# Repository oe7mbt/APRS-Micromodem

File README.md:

# APRS-Micromodem

Die Schaltung basiert auf der Entwicklung von Mark Qvist aus Dänemark (http://unsigned.io/projects/microaprs/), der auch die Firmware als Open-Source bereitstellt. Ebenso gibt es eine Libary für eigene Entwicklungen in der Arduino-Entwicklungsumgebung.

Ich habe diese Schaltung für meine Zwecke angepasst und dafür eine Platine erstellt, die einerseits auf einem kostengünstigen Arduino Nano basiert und andererseits für Experimente leicht erweiterbar ist.

Die Pins des Arduino sind (z.B für den Anschluß eines GPS-Modules oder eines Displays) auf einer Pinleiste direkt abgrefbar. Weiters gibt es auch eine I2C-Schnittstelle für die Kommunikation mit weiterer Hardware.

73 de Marco, OE7MBT

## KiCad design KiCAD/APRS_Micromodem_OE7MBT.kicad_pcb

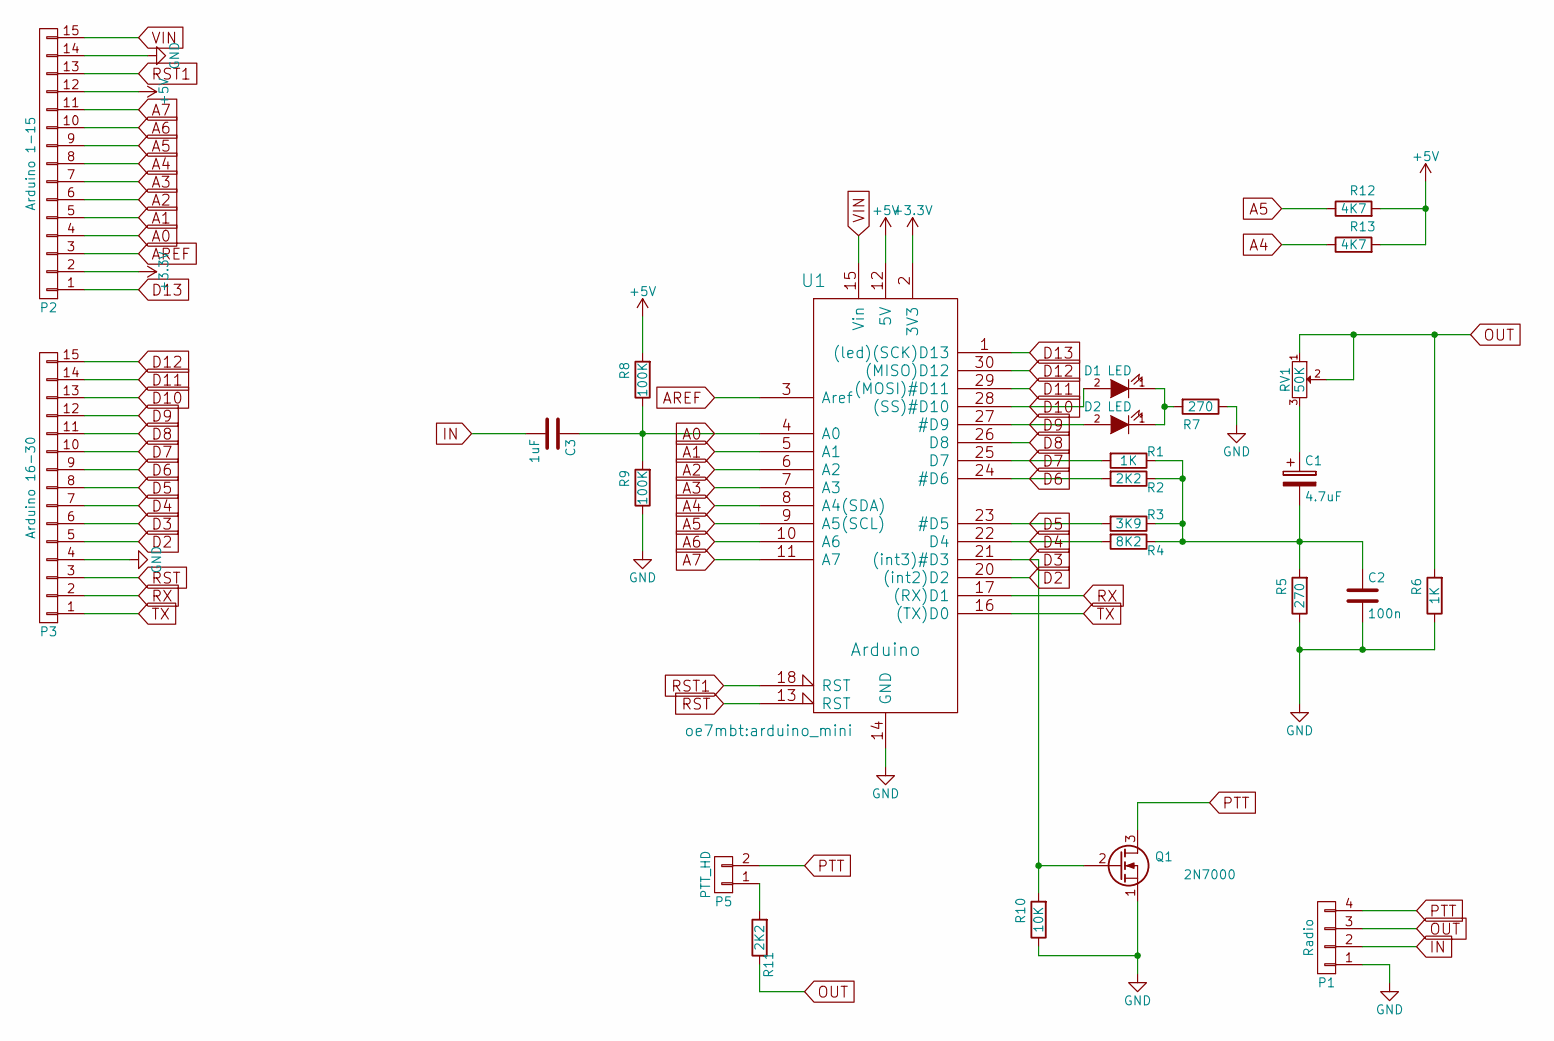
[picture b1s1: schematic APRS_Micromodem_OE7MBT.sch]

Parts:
C1: 4.7uF; C_Radial_D5_L11_P2
C2: 100n; C_0805_HandSoldering
C3: 1uF; C_0805_HandSoldering
D1: LED; led_3mm_green
D2: LED; led_3mm_red
P1: Radio; Pin_Header_Straight_1x04
P2: Arduino 1-15; Pin_Header_Straight_1x15_Pitch2.54mm
P3: Arduino 16-30; Pin_Header_Straight_1x15_Pitch2.54mm
P5: PTT_HD; Pin_Header_Straight_1x02
Q1: 2N7000; TO-92_Inline_Wide
R1, R6: 1K; R_0805_HandSoldering
R2, R11: 2K2; R_0805_HandSoldering
R3: 3K9; R_0805_HandSoldering
R4: 8K2; R_0805_HandSoldering
R5, R7: 270; R_0805_HandSoldering
R8, R9: 100K; R_0805_HandSoldering
R10: 10K; R_0805_HandSoldering
R12, R13: 4K7; R_0805_HandSoldering
RV1: 50K; trimmer_piher_pt10xv10
U1: Arduino; arduino_mini

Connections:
+3V3: P2.2, U1.2 (3V3)
+5V: P2.12, R8.2, R12.2, R13.2, U1.12 (5V)
A0: C3.1, P2.4, R8.1, R9.2, U1.4 (A0)
A1: P2.5, U1.5 (A1)
A2: P2.6, U1.6 (A2)
A3: P2.7, U1.7 (A3)
A4: P2.8, R13.1, U1.8 (A4(SDA))
A5: P2.9, R12.1, U1.9 (A5(SCL))
A6: P2.10, U1.10 (A6)
A7: P2.11, U1.11 (A7)
AREF: P2.3, U1.3 (Aref)
D2: P3.5, U1.20 ((int2)D2)
D3: P3.6, Q1.2 (G), R10.2, U1.21 ((int3)#D3)
D4: P3.7, R4.2, U1.22 (D4)
D5: P3.8, R3.2, U1.23 (#D5)
D6: P3.9, R2.2, U1.24 (#D6)
D7: P3.10, R1.2, U1.25 (D7)
D8: P3.11, U1.26 (D8)
D9: D2.2 (A), P3.12, U1.27 (#D9)
D10: D1.2 (A), P3.13, U1.28 ((SS)#D10)
D11: P3.14, U1.29 ((MOSI)#D11)
D12: P3.15, U1.30 ((MISO)D12)
D13: P2.1, U1.1 ((led)(SCK)D13)
GND: C2.2, P1.1, P2.14, P3.4, Q1.1 (S), R5.1, R6.1, R7.1, R9.1, R10.1, U1.14 (GND), U1.19 (GND)
IN: C3.2, P1.2
unnamed: C1.1, RV1.3
unnamed: C1.2, C2.1, R1.1, R2.1, R3.1, R4.1, R5.2
unnamed: D1.1 (K), D2.1 (K), R7.2
unnamed: P5.1, R11.2
OUT: P1.3, R6.2, R11.1, RV1.1, RV1.2
PTT: P1.4, P5.2, Q1.3 (D)
RST: P3.3, U1.13 (RST)
RST1: P2.13, U1.18 (RST)
RX: P3.2, U1.17 ((RX)D1)
TX: P3.1, U1.16 ((TX)D0)
VIN: P2.15, U1.15 (Vin)

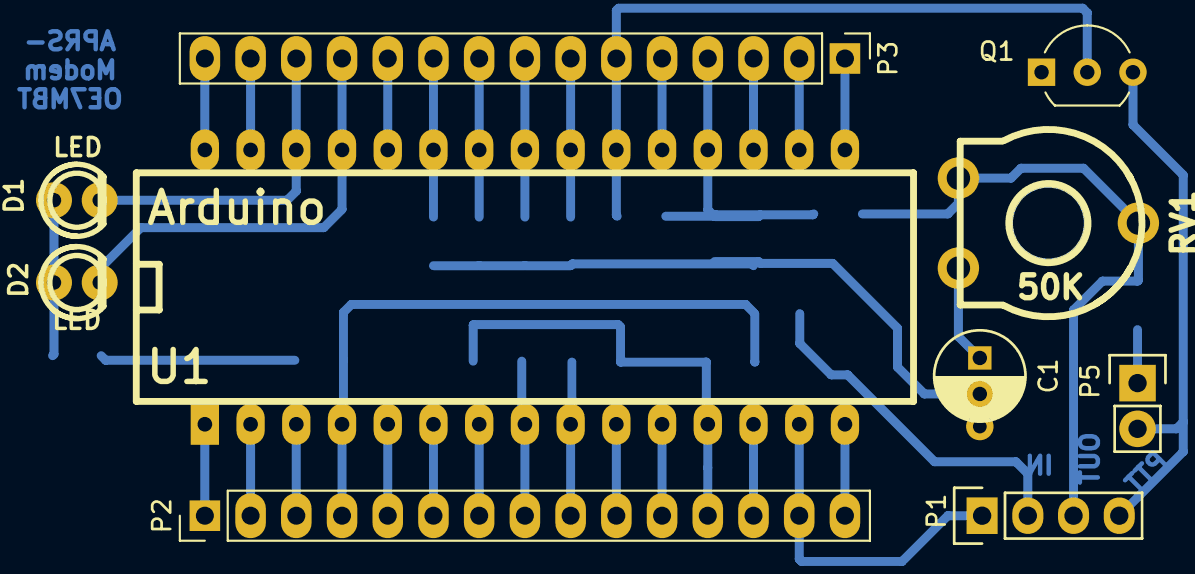
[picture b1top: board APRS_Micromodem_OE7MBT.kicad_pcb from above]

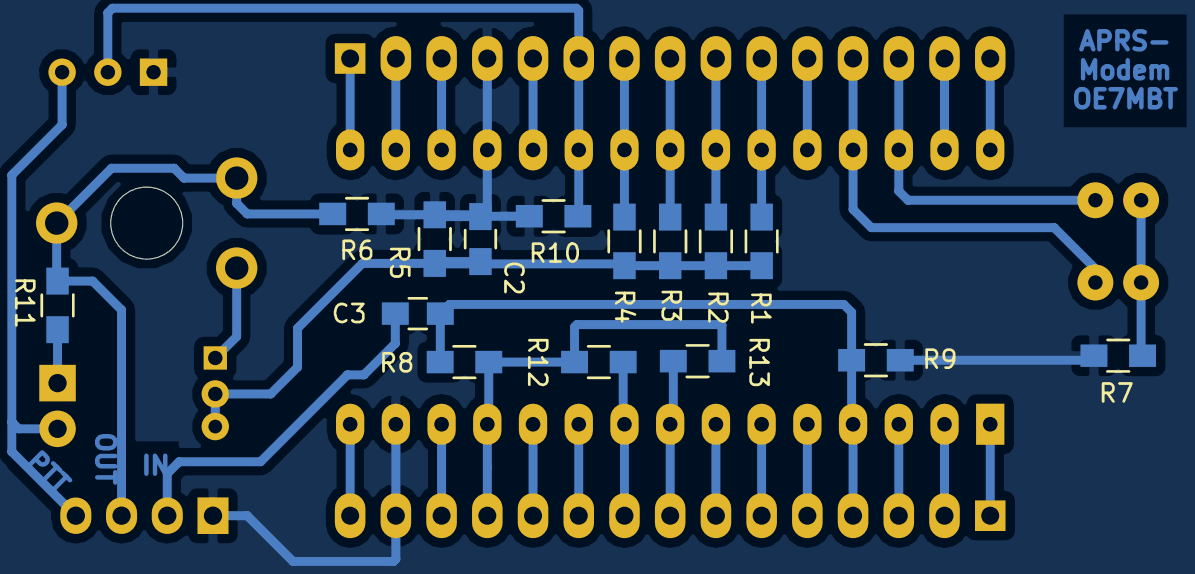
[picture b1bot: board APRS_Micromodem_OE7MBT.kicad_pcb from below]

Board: 2 copper layers, 25 parts (15 on the bottom side), 36 nets.

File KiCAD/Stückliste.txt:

Anzahl	Bezeichner	Wert	Bauteil
			
2	R1,R6	1K	SMD 0805
2	R2,R11	2K2	SMD 0805
1	R3	3K9	SMD 0805
1	R4	8K2	SMD 0805
2	R5,R7	270	SMD 0805
2	R8,R9	100K	SMD 0805
1	R10	10K	SMD 0805
			
1	C1	4.7uF	Elko RM 2
1	C2	100nF	SMD 0805
1	C3	1uF	SMD 0805
			
1	Q1	2N7000	TO-92
1	D1	LED	LED 3mm Grün
1	D2	LED	LED 3mm Rot
1	RV1	50K	Trimmer Piher PT10
			
			
			
2	R12,R13	4K7	SMD 0805
			
			
1	P1	Radio	Pinleiste 1x4
1	P2	Arduino 1-15	Pinleiste 1x15
1	P3	Arduino 16-30	Pinleiste 1x15
1	P5	PTT_HD	Pinleiste 1x2
			
1	U1	Arduino	Arduino Nano

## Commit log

2017-05-03 Create Pictures
2017-05-03 Update Pictures
2017-05-03 Create test
2017-05-03 Create 1
